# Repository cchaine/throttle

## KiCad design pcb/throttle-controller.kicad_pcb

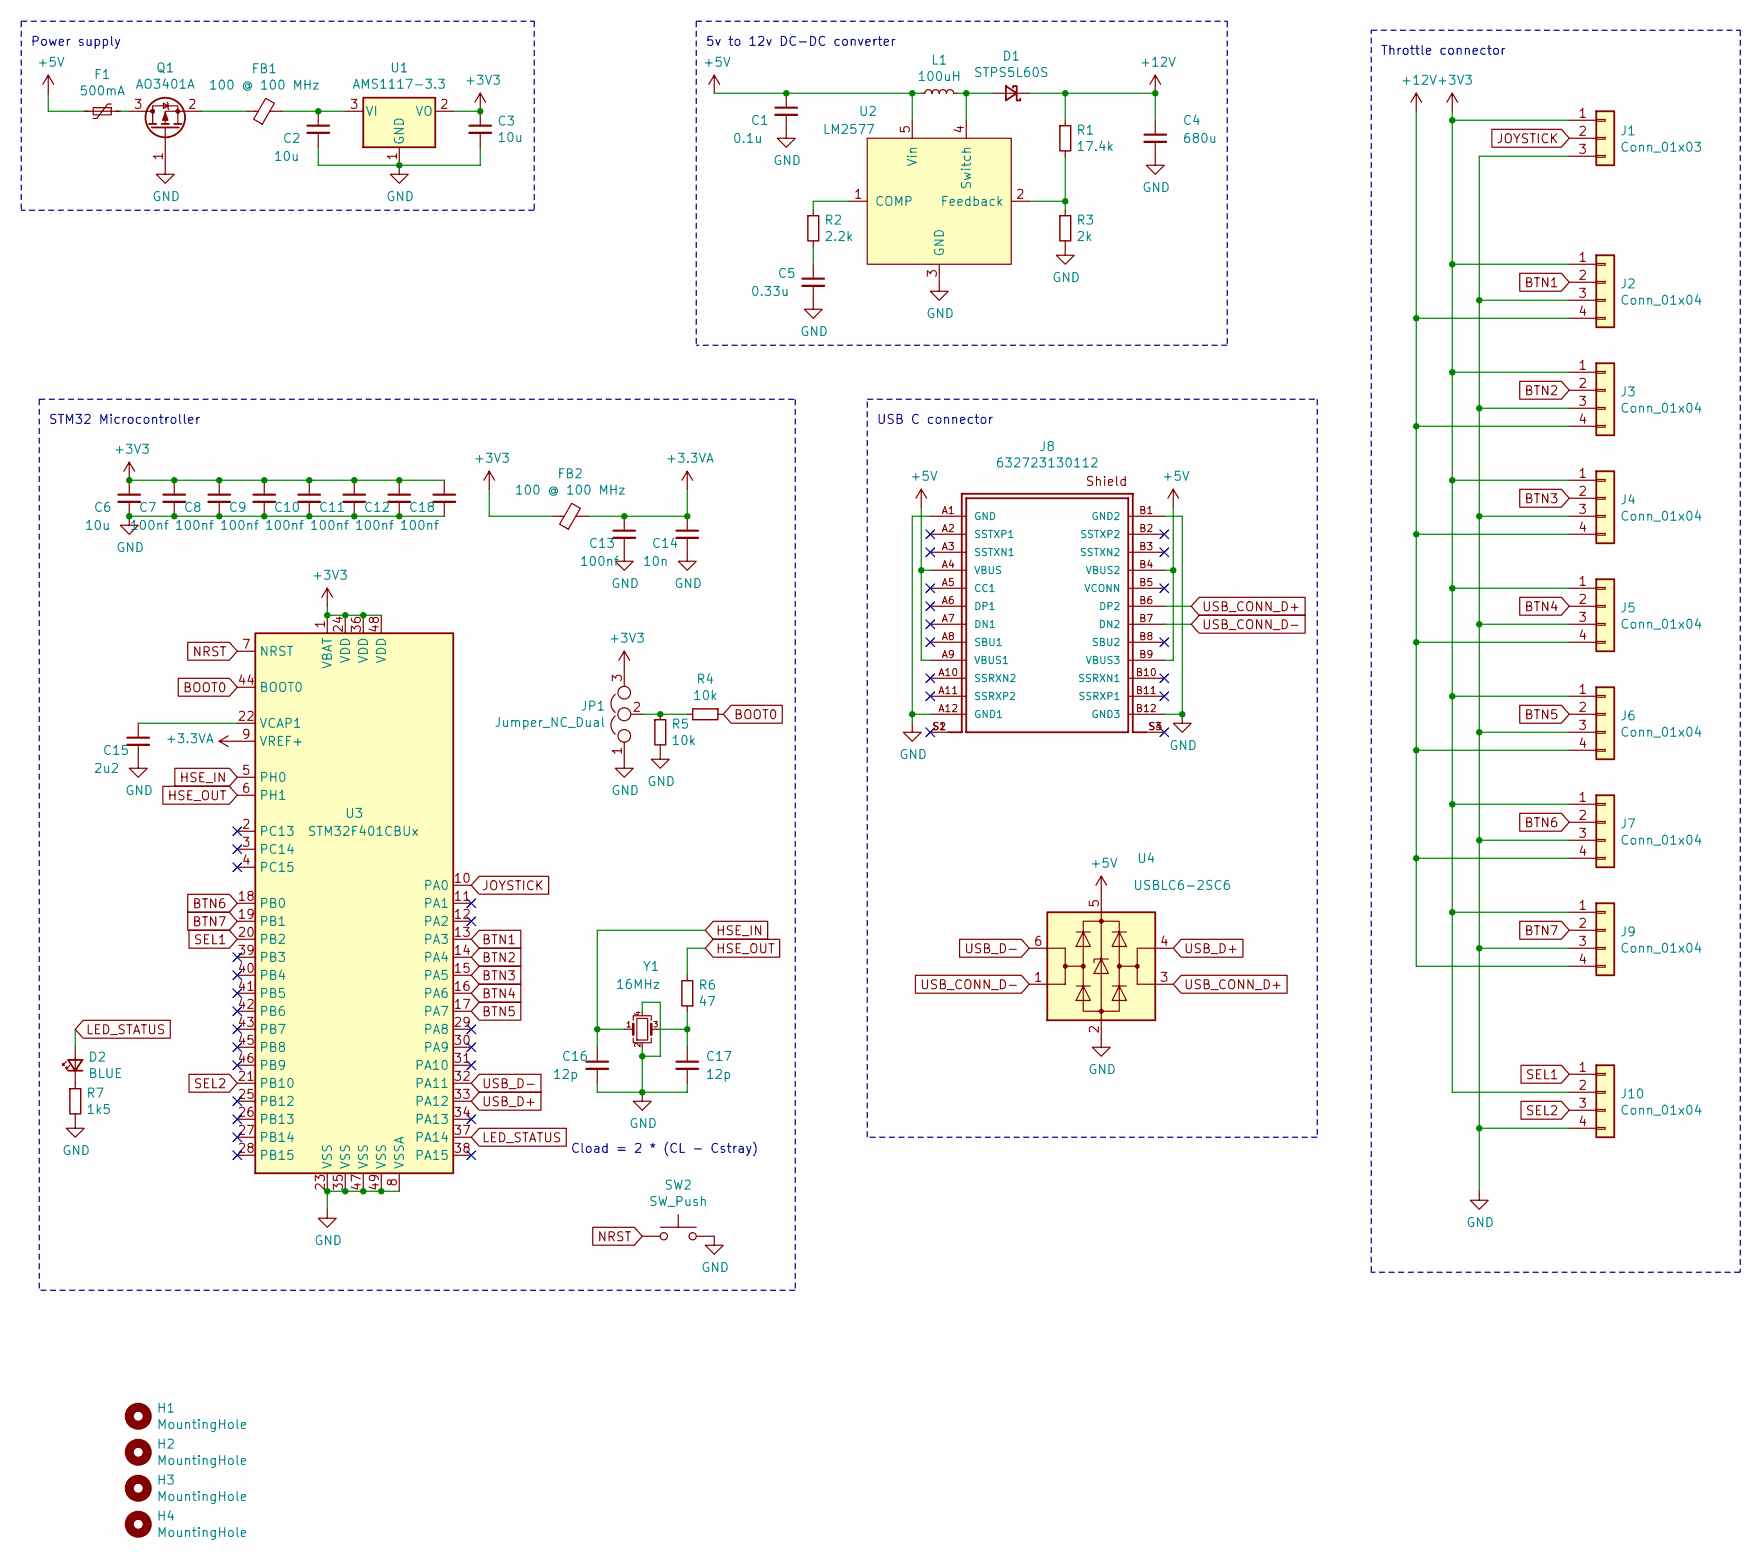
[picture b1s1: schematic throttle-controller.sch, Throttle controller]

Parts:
C1: 0.1u; C_1206_3216Metric
C2, C3: 10u; C_1206_3216Metric
C4: 680u; C_1206_3216Metric
C5: 0.33u; C_1206_3216Metric
C6: 10u; C_0402_1005Metric
C7, C8, C9, C10, C11, C12, C13, C18: 100nf; C_0402_1005Metric
C14: 10n; C_0402_1005Metric
C15: 2u2; C_0402_1005Metric
C16, C17: 12p; C_0402_1005Metric
D1: STPS5L60S; DO-214AB
D2: BLUE; LED_0805_2012Metric
F1: 500mA; Fuse_1206_3216Metric
FB1, FB2: 100 @ 100 MHz; L_0805_2012Metric
H1, H2, H3, H4: MountingHole; MountingHole_2.2mm_M2
J1: Conn_01x03; JST_XH_B3B-XH-A_1x03_P2.50mm_Vertical
J2, J3, J4, J5, J6, J7, J9, J10: Conn_01x04; JST_XH_B4B-XH-A_1x04_P2.50mm_Vertical
J8: 632723130112; PART-NUMBER 632723130112
JP1: Jumper_NC_Dual; PinHeader_1x03_P1.27mm_Horizontal
L1: 100uH; L_Bourns_SRR1210A
Q1: AO3401A; SOT-23
R1: 17.4k; R_1206_3216Metric
R2: 2.2k; R_1206_3216Metric
R3: 2k; R_1206_3216Metric
R4, R5: 10k; R_0402_1005Metric
R6: 47; R_0402_1005Metric
R7: 1k5; R_0603_1608Metric
SW2: SW_Push; Panasonic_EVQPUJ_EVQPUA
U1: AMS1117-3.3; SOT-223-3_TabPin2
U2: LM2577; TO-263-5_TabPin6
U3: STM32F401CBUx; QFN-48-1EP_7x7mm_P0.5mm_EP5.6x5.6mm
U4: USBLC6-2SC6; SOT-23-6
Y1: 16MHz; Crystal_SMD_3225-4Pin_3.2x2.5mm

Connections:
+3.3VA: C13.1, C14.1, FB2.2, U3.9 (VREF+)
+3V3: C3.1, C6.1, C7.1, C8.1, C9.1, C10.1, C11.1, C12.1, C18.1, FB2.1, J1.1, J2.1, J3.1, J4.1, J5.1, J6.1, J7.1, J9.1, J10.2, JP1.3, U1.2 (VO), U3.1 (VBAT), U3.24 (VDD), U3.36 (VDD), U3.48 (VDD)
+5V: C1.1, F1.2, J8.A4 (VBUS), J8.A9 (VBUS1), J8.B4 (VBUS2), J8.B9 (VBUS3), L1.1, U2.5 (Vin), U4.5 (VBUS)
+12V: C4.1, D1.1 (K), J2.4, J3.4, J4.4, J5.4, J6.4, J7.4, J9.4, R1.1
BOOT0: R4.1, U3.44 (BOOT0)
BTN1: J2.2, U3.13 (PA3)
BTN2: J3.2, U3.14 (PA4)
BTN3: J4.2, U3.15 (PA5)
BTN4: J5.2, U3.16 (PA6)
BTN5: J6.2, U3.17 (PA7)
BTN6: J7.2, U3.18 (PB0)
BTN7: J9.2, U3.19 (PB1)
GND: C1.2, C2.2, C3.2, C4.2, C5.2, C6.2, C7.2, C8.2, C9.2, C10.2, C11.2, C12.2, C13.2, C14.2, C15.2, C16.2, C17.2, C18.2, J1.3, J2.3, J3.3, J4.3, J5.3, J6.3, J7.3, J8.A1 (GND), J8.A12 (GND1), J8.B1 (GND2), J8.B12 (GND3), J9.3, J10.4, JP1.1, Q1.1 (G), R3.2, R5.2, R7.2, SW2.2, U1.1 (GND), U2.3 (GND), U3.8 (VSSA), U3.23 (VSS), U3.35 (VSS), U3.47 (VSS), U3.49 (VSS), U4.2 (GND), Y1.2, Y1.4
HSE_IN: C16.1, U3.5 (PH0), Y1.1
HSE_OUT: R6.2, U3.6 (PH1)
JOYSTICK: J1.2, U3.10 (PA0)
LED_STATUS: D2.2 (A), U3.37 (PA14)
NRST: SW2.1, U3.7 (NRST)
unnamed: C2.1, FB1.2, U1.3 (VI)
unnamed: C5.1, R2.2
unnamed: C15.1, U3.22 (VCAP1)
unnamed: C17.1, R6.1, Y1.3
unnamed: D1.2 (A), L1.2, U2.4 (Switch)
unnamed: D2.1 (K), R7.1
unnamed: F1.1, Q1.3 (D)
unnamed: FB1.1, Q1.2 (S)
unnamed: J8.S1, J8.S2
unnamed: J8.S3, J8.S4
unnamed: JP1.2, R4.2, R5.1
unnamed: R1.2, R3.1, U2.2 (Feedback)
unnamed: R2.1, U2.1 (COMP)
SEL1: J10.1, U3.20 (PB2)
SEL2: J10.3, U3.21 (PB10)
USB_CONN_D+: J8.B6 (DP2), U4.3 (I/O2)
USB_CONN_D-: J8.B7 (DN2), U4.1 (I/O1)
USB_D+: U3.33 (PA12), U4.4 (I/O2)
USB_D-: U3.32 (PA11), U4.6 (I/O1)

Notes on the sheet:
Power supply
Cload = 2 * (CL - Cstray)
STM32 Microcontroller
5v to 12v DC-DC converter
USB C connector
Throttle connector

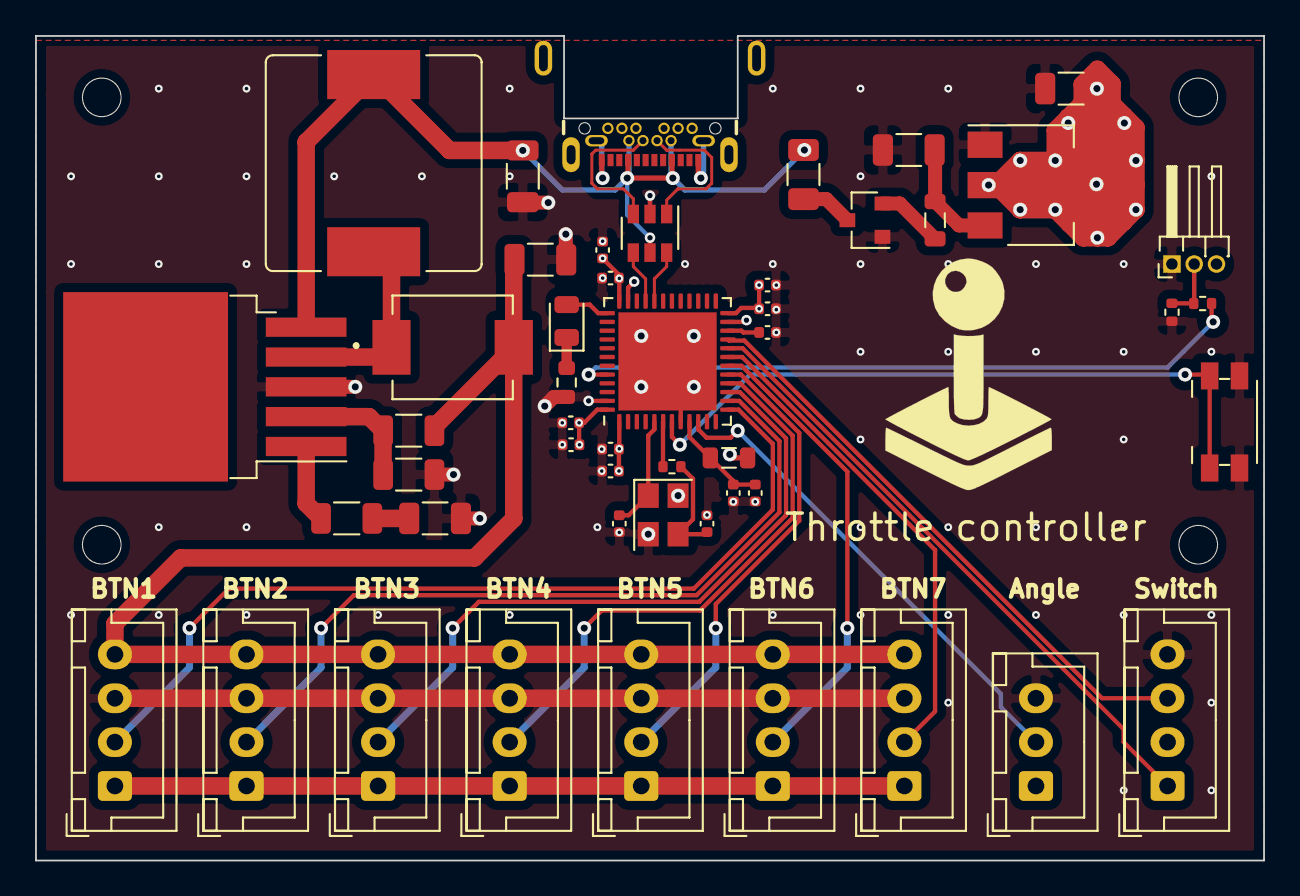
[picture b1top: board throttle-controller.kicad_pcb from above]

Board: 4 copper layers, 70.0 x 47.0 mm, 53 parts (0 on the bottom side), 37 nets.

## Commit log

2021-02-02 added the throttle controller pcb
